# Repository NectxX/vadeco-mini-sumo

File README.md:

# vadeco-mini-sumo
Repositório destinado à criação da placa de circuito impresso

Neste esquemático, fora realizada conexão dos sensores de linha e distância (conectores), de duas pontes H, do microstart remoto e do regulador de tensão ajustável com a plataforma Arduino.

A saber:
Para os sensores de linha, de acordo com o módulo selecionado para o projeto, há a opção de utilizar as saídas digitais ou analógicas. Fora utilizado as saídas analógicas, pois a prioridade dos pinos digitais do arduino foi destinado aos sensores de distância.

Diferenças do Gundabad para o Vadeco:
-Não foi utilizado CI's de porta NOT e AND, pois houve margem suficiente de pinos para conectar todos os dispositivos ao Arduino. Logo, toda a estratégia de funcionamento do robô viria exclusivamente do código de programação.
-O motor e o Arduino no Vadeco são alimentados pela mesma tensão de 6V oriunda do regulador LM2596. Diferentemente do Gundabad, que alimenta os motores diretamente com a tensão da bateria.

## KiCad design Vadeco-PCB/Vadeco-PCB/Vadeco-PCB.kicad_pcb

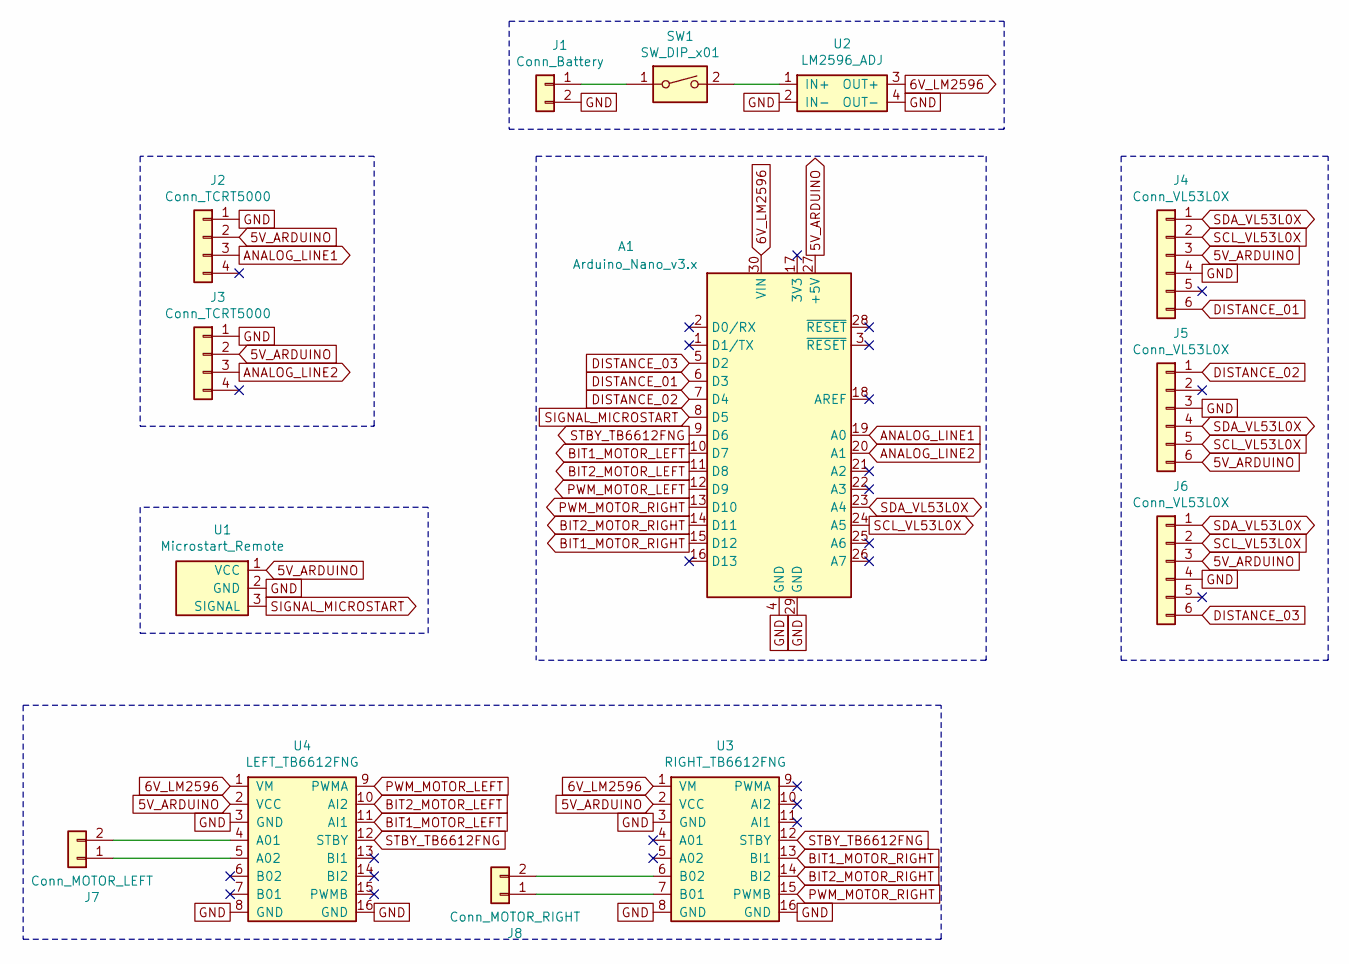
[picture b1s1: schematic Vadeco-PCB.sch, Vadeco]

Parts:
A1: Arduino_Nano_v3.x; Arduino_Nano
J1: Conn_Battery; PinHeader_1x02_P1.00mm_Horizontal
J2, J3: Conn_TCRT5000; PinHeader_1x04_P1.00mm_Horizontal
J4, J5, J6: Conn_VL53L0X; PinHeader_1x06_P1.00mm_Horizontal
J7: Conn_MOTOR_LEFT; PinHeader_1x02_P1.00mm_Horizontal
J8: Conn_MOTOR_RIGHT; PinHeader_1x02_P1.00mm_Horizontal
SW1: SW_DIP_x01; SW_DIP_SPSTx01_Slide_9.78x4.72mm_W7.62mm_P2.54mm
U1: Microstart_Remote; MICROSTART_MODULE
U2: LM2596_ADJ
U3: RIGHT_TB6612FNG; TB6612FNG
U4: LEFT_TB6612FNG; TB6612FNG

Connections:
5V_ARDUINO: A1.27 (+5V), J2.2, J3.2, J4.3, J5.6, J6.3, U1.1 (VCC), U3.2 (VCC), U4.2 (VCC)
6V_LM2596: A1.30 (VIN), U2.3 (OUT+), U3.1 (VM), U4.1 (VM)
ANALOG_LINE1: A1.19 (A0), J2.3
ANALOG_LINE2: A1.20 (A1), J3.3
BIT1_MOTOR_LEFT: A1.10 (D7), U4.11 (AI1)
BIT1_MOTOR_RIGHT: A1.15 (D12), U3.13 (BI1)
BIT2_MOTOR_LEFT: A1.11 (D8), U4.10 (AI2)
BIT2_MOTOR_RIGHT: A1.14 (D11), U3.14 (BI2)
DISTANCE_01: A1.6 (D3), J4.6
DISTANCE_02: A1.7 (D4), J5.1
DISTANCE_03: A1.5 (D2), J6.6
GND: A1.4 (GND), A1.29 (GND), J1.2, J2.1, J3.1, J4.4, J5.3, J6.4, U1.2 (GND), U2.2 (IN-), U2.4 (OUT-), U3.3 (GND), U3.8 (GND), U3.16 (GND), U4.3 (GND), U4.8 (GND), U4.16 (GND)
unnamed: J1.1, SW1.1
unnamed: J7.1, U4.5 (A02)
unnamed: J7.2, U4.4 (A01)
unnamed: J8.1, U3.7 (B01)
unnamed: J8.2, U3.6 (B02)
unnamed: SW1.2, U2.1 (IN+)
PWM_MOTOR_LEFT: A1.12 (D9), U4.9 (PWMA)
PWM_MOTOR_RIGHT: A1.13 (D10), U3.15 (PWMB)
SCL_VL53L0X: A1.24 (A5), J4.2, J5.5, J6.2
SDA_VL53L0X: A1.23 (A4), J4.1, J5.4, J6.1
SIGNAL_MICROSTART: A1.8 (D5), U1.3 (SIGNAL)
STBY_TB6612FNG: A1.9 (D6), U3.12 (STBY), U4.12 (STBY)

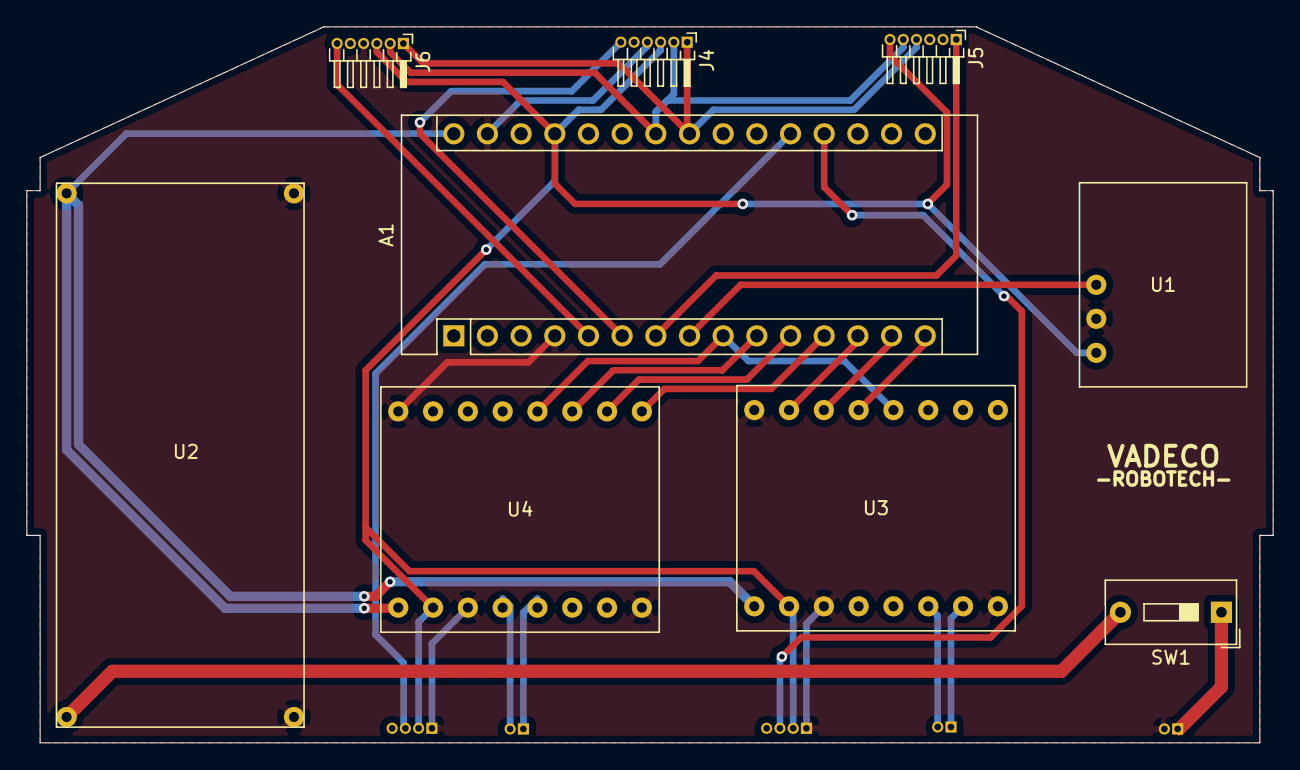
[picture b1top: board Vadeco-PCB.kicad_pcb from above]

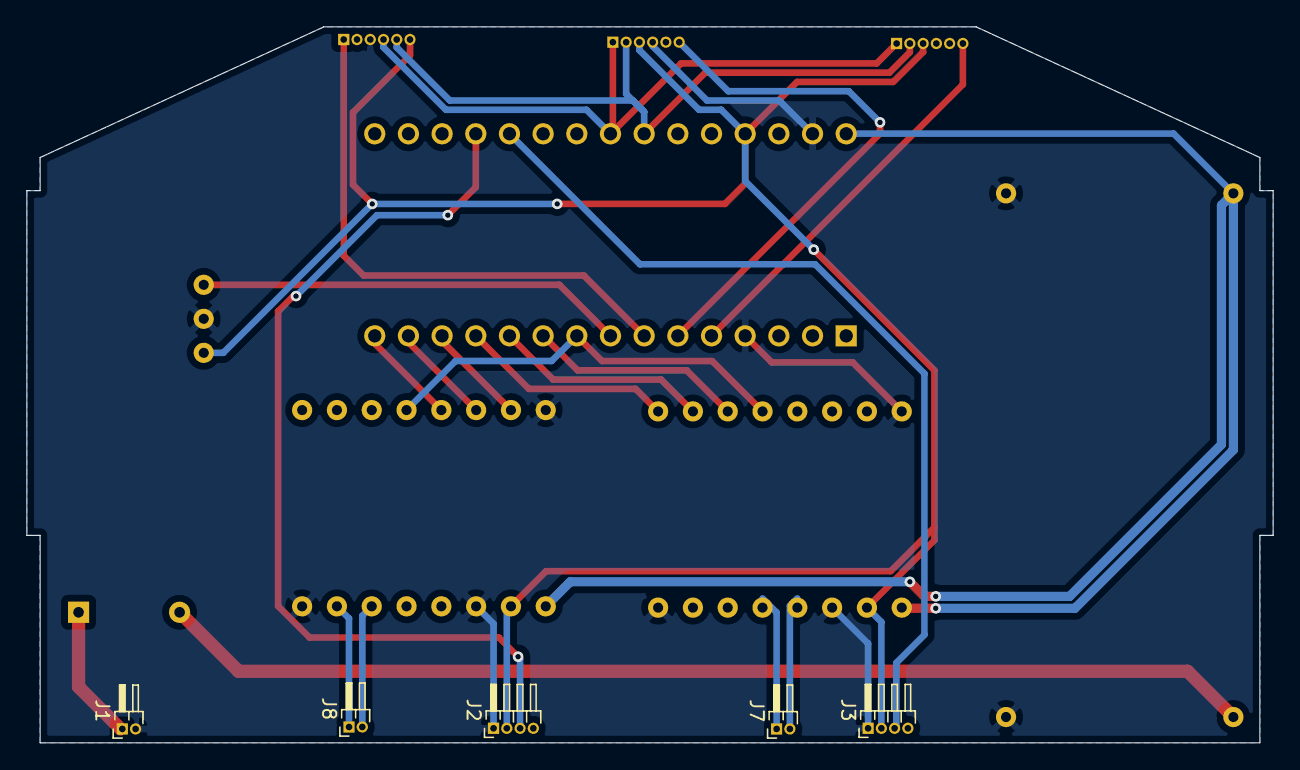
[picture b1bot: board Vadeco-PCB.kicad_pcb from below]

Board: 2 copper layers, 94.0 x 54.0 mm, 14 parts (5 on the bottom side), 24 nets.

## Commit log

2021-05-30 schematic without arduino connection and h bridge
2021-05-30 schematic done
2021-05-30 updating README
2021-05-30 associating footprint lm2596
2021-05-31 microstart and tb6612fng footprints
2021-05-31 all footprints associated and placed to PCB
2021-06-01 final project v1
2021-06-01 generating topside and backside view
2021-06-03 schematic v3 and PCB v2
